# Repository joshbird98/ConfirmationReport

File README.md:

"# ConfirmationReport" 
Appendix A1 for confirmation report 
"Developments in Ion Beam Technology for Isotope Engineering at Ultra-Low Energy"
Contains hardware and software design files.

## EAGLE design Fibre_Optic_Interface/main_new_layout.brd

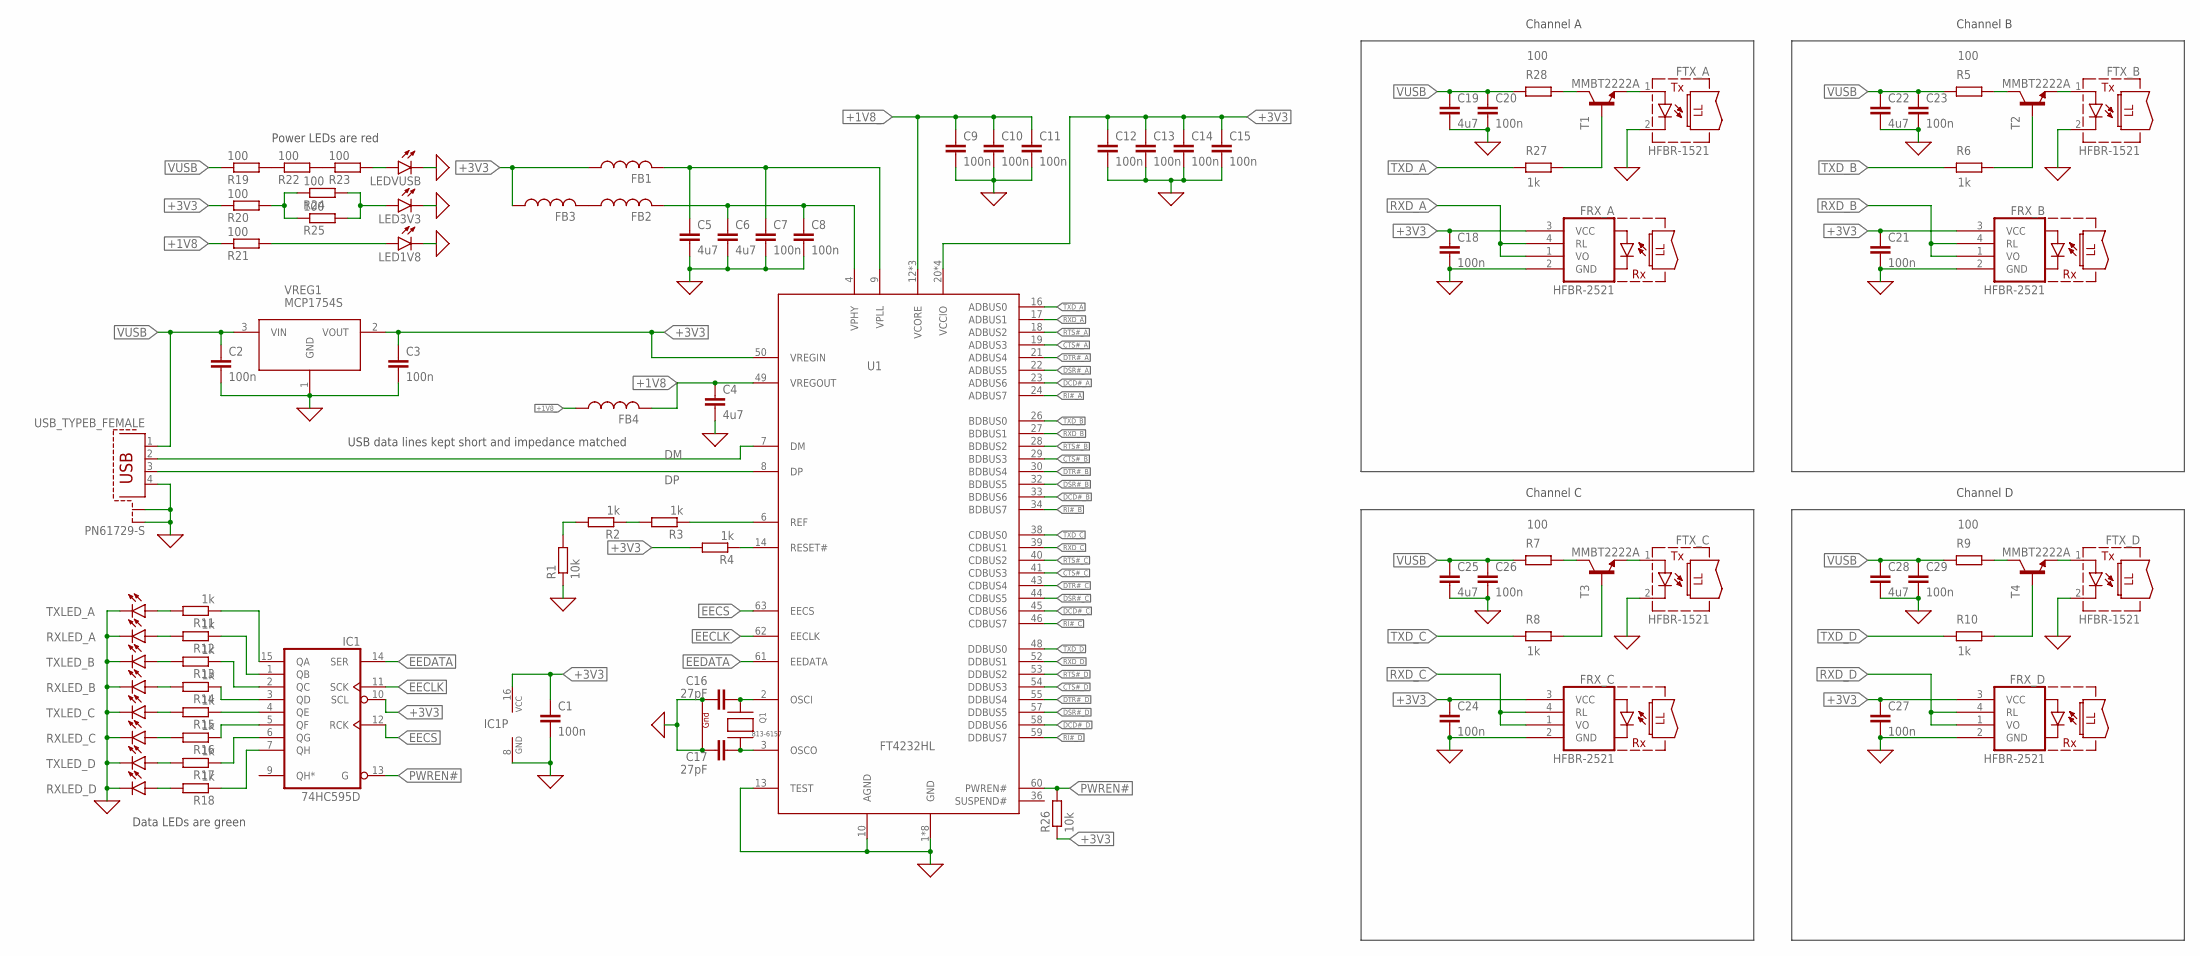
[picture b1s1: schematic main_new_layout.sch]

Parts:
C1, C2, C3, C7, C8, C9, C10, C11, C12, C13, C14, C15, C18, C20, C21, C23, C24, C26, C27, C29: 100n; C0805
C4, C5, C6, C19, C22, C25, C28: 4u7; C0805
C16, C17: 27pF; C0805
FB1, FB2, FB3, FB4: FERRITE; R0805
FRX_A: HFBR-2521; HFBR-15X3
FRX_B: HFBR-2521; HFBR-15X3
FRX_C: HFBR-2521; HFBR-15X3
FRX_D: HFBR-2521; HFBR-15X3
FTX_A: HFBR-1521; HFBR-15X3
FTX_B: HFBR-1521; HFBR-15X3
FTX_C: HFBR-1521; HFBR-15X3
FTX_D: HFBR-1521; HFBR-15X3
IC1: 74HC595D; SO16
LED1V8, LED3V3: LEDCHIP-LED0805; CHIP-LED0805
LEDVUSB: LEDCHIP-LED0805; CHIP-LED0805
Q1: XTAL-4-3225; NX3225
R1, R26: 10k; R0805
R2, R3, R4, R6, R8, R10, R11, R12, R13, R14, R15, R16, R17, R18, R27: 1k; R0805
R5, R7, R9, R19, R20, R21, R22, R23, R24, R25, R28: 100; R0805
RXLED_A: LEDCHIP-LED0805; CHIP-LED0805
RXLED_B: LEDCHIP-LED0805; CHIP-LED0805
RXLED_C: LEDCHIP-LED0805; CHIP-LED0805
RXLED_D: LEDCHIP-LED0805; CHIP-LED0805
T1, T2, T3, T4: MMBT2222A; SOT23-BEC
TXLED_A: LEDCHIP-LED0805; CHIP-LED0805
TXLED_B: LEDCHIP-LED0805; CHIP-LED0805
TXLED_C: LEDCHIP-LED0805; CHIP-LED0805
TXLED_D: LEDCHIP-LED0805; CHIP-LED0805
U1: FT4232HL; LQFP-ST-64-2
USB_TYPEB_FEMALE: PN61729-S
VREG1: MCP1754S; SOT23

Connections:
0: C1.2, C2.2, C3.2, C4.2, C5.2, C6.2, C7.2, C8.2, C9.2, C10.2, C11.2, C12.2, C13.2, C14.2, C15.2, C16.2, C17.2, C18.2, C19.2, C20.2, C21.2, C22.2, C23.2, C24.2, C25.2, C26.2, C27.2, C28.2, C29.2, FRX_A.2 (GND), FRX_B.2 (GND), FRX_C.2 (GND), FRX_D.2 (GND), FTX_A.2 (C), FTX_B.2 (C), FTX_C.2 (C), FTX_D.2 (C), IC1.8 (GND), LED1V8.C, LED3V3.C, LEDVUSB.C, Q1.2 (G2), Q1.4 (G1), R1.1, RXLED_A.C, RXLED_B.C, RXLED_C.C, RXLED_D.C, TXLED_A.C, TXLED_B.C, TXLED_C.C, TXLED_D.C, U1.1 (GND), U1.5 (GND), U1.10 (AGND), U1.11 (GND), U1.13 (TEST), U1.15 (GND), U1.25 (GND), U1.35 (GND), U1.47 (GND), U1.51 (GND), USB_TYPEB_FEMALE.4, USB_TYPEB_FEMALE.S1, USB_TYPEB_FEMALE.S2, VREG1.1 (GND)
+1V8: C4.1, FB4.2, R21.1, U1.49 (VREGOUT)
+1V8_: C9.1, C10.1, C11.1, FB4.1, U1.12 (VCORE), U1.37 (VCORE), U1.64 (VCORE)
+3V3: C1.1, C3.1, C12.1, C13.1, C14.1, C15.1, C18.1, C21.1, C24.1, C27.1, FB1.1, FB3.1, FRX_A.3 (VCC), FRX_B.3 (VCC), FRX_C.3 (VCC), FRX_D.3 (VCC), IC1.10 (SCL), IC1.16 (VCC), R4.2, R20.1, R26.1, U1.20 (VCCIO), U1.31 (VCCIO), U1.42 (VCCIO), U1.50 (VREGIN), U1.56 (VCCIO), VREG1.2 (VOUT)
CTS#_A: U1.19 (ADBUS3)
CTS#_B: U1.29 (BDBUS3)
CTS#_C: U1.41 (CDBUS3)
CTS#_D: U1.54 (DDBUS3)
DCD#_A: U1.23 (ADBUS6)
DCD#_B: U1.33 (BDBUS6)
DCD#_C: U1.45 (CDBUS6)
DCD#_D: U1.58 (DDBUS6)
DM: U1.7 (DM), USB_TYPEB_FEMALE.2
DP: U1.8 (DP), USB_TYPEB_FEMALE.3
DSR#_A: U1.22 (ADBUS5)
DSR#_B: U1.32 (BDBUS5)
DSR#_C: U1.44 (CDBUS5)
DSR#_D: U1.57 (DDBUS5)
DTR#_A: U1.21 (ADBUS4)
DTR#_B: U1.30 (BDBUS4)
DTR#_C: U1.43 (CDBUS4)
DTR#_D: U1.55 (DDBUS4)
EECLK: IC1.11 (SCK), U1.62 (EECLK)
EECS: IC1.12 (RCK), U1.63 (EECS)
EEDATA: IC1.14 (SER), U1.61 (EEDATA)
unnamed: LEDVUSB.A, R23.2
unnamed: LED3V3.A, R24.2, R25.2
unnamed: R27.2, T1.B
unnamed: C5.1, C7.1, FB1.2, U1.9 (VPLL)
unnamed: C6.1, C8.1, FB2.2, U1.4 (VPHY)
unnamed: R28.2, T1.C
unnamed: C17.1, Q1.3 (X2), U1.3 (OSCO)
unnamed: C16.1, Q1.1 (X1), U1.2 (OSCI)
unnamed: R3.1, U1.6 (REF)
unnamed: R4.1, U1.14 (RESET#)
unnamed: R2.1, R3.2
unnamed: R1.2, R2.2
unnamed: R6.2, T2.B
unnamed: R5.2, T2.C
unnamed: FTX_B.1 (A), T2.E
unnamed: FTX_A.1 (A), T1.E
unnamed: R8.2, T3.B
unnamed: R7.2, T3.C
unnamed: FTX_C.1 (A), T3.E
unnamed: R10.2, T4.B
unnamed: R9.2, T4.C
unnamed: FTX_D.1 (A), T4.E
unnamed: FB2.1, FB3.2
unnamed: IC1.15 (QA), R11.1
unnamed: IC1.1 (QB), R12.1
unnamed: IC1.2 (QC), R13.1
unnamed: LED1V8.A, R21.2
unnamed: IC1.3 (QD), R14.1
unnamed: IC1.4 (QE), R15.1
unnamed: IC1.5 (QF), R16.1
unnamed: IC1.6 (QG), R17.1
unnamed: IC1.7 (QH), R18.1
unnamed: R19.2, R22.1
unnamed: R11.2, TXLED_A.A
unnamed: R12.2, RXLED_A.A
unnamed: R13.2, TXLED_B.A
unnamed: R14.2, RXLED_B.A
unnamed: R15.2, TXLED_C.A
unnamed: R16.2, RXLED_C.A
unnamed: R17.2, TXLED_D.A
unnamed: R18.2, RXLED_D.A
unnamed: R22.2, R23.1
unnamed: R20.2, R24.1, R25.1
PWREN#: IC1.13 (G), R26.2, U1.60 (PWREN#)
RI#_A: U1.24 (ADBUS7)
RI#_B: U1.34 (BDBUS7)
RI#_C: U1.46 (CDBUS7)
RI#_D: U1.59 (DDBUS7)
RTS#_A: U1.18 (ADBUS2)
RTS#_B: U1.28 (BDBUS2)
RTS#_C: U1.40 (CDBUS2)
RTS#_D: U1.53 (DDBUS2)
RXD_A: FRX_A.1 (VO), FRX_A.4 (RL), U1.17 (ADBUS1)
RXD_B: FRX_B.1 (VO), FRX_B.4 (RL), U1.27 (BDBUS1)
RXD_C: FRX_C.1 (VO), FRX_C.4 (RL), U1.39 (CDBUS1)
RXD_D: FRX_D.1 (VO), FRX_D.4 (RL), U1.52 (DDBUS1)
TXD_A: R27.1, U1.16 (ADBUS0)
TXD_B: R6.1, U1.26 (BDBUS0)
TXD_C: R8.1, U1.38 (CDBUS0)
TXD_D: R10.1, U1.48 (DDBUS0)
VUSB: C2.1, C19.1, C20.1, C22.1, C23.1, C25.1, C26.1, C28.1, C29.1, R5.1, R7.1, R9.1, R19.1, R28.1, USB_TYPEB_FEMALE.1, VREG1.3 (VIN)

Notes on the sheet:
USB data lines kept short and impedance matched
Channel A
Channel B
Channel C
Channel D
Power LEDs are red
Data LEDs are green
813-6157

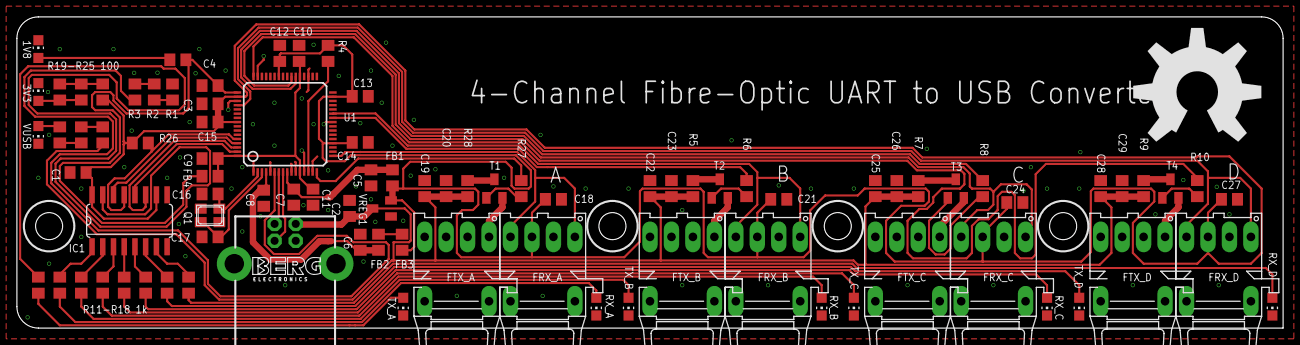
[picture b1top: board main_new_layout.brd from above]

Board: 2 copper layers, 149.9 x 36.8 mm, 89 parts (0 on the bottom side), 62 nets.

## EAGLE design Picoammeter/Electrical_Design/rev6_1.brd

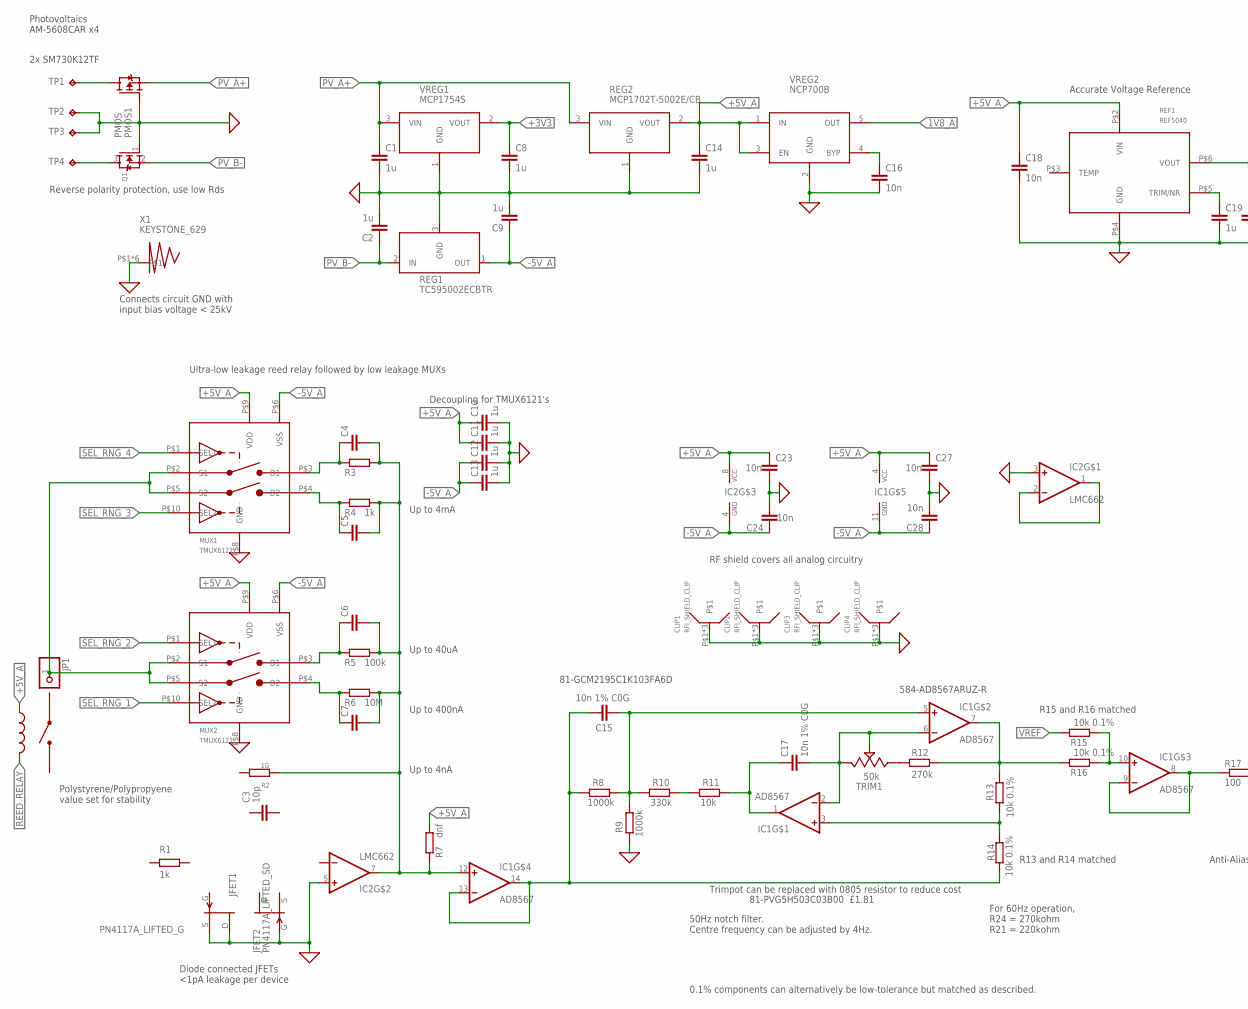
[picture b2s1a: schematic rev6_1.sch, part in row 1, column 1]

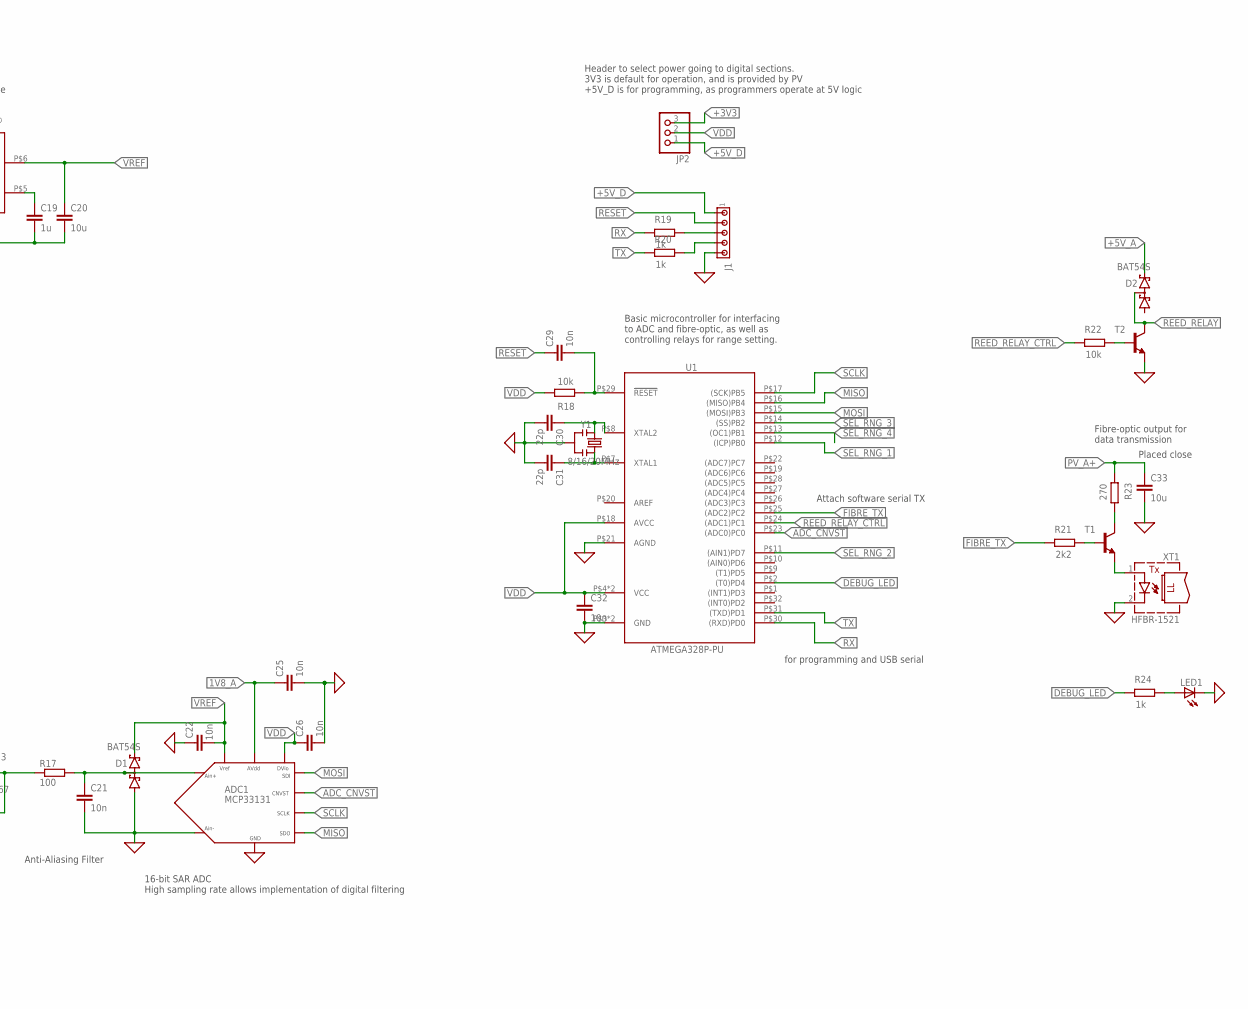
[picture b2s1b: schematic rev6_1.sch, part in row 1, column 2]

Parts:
ADC1: MCP33131; MSOP10
C1, C2, C8, C9, C10, C11, C12, C13, C14, C19: 1u; C0805
C4, C5, C6, C7: C-EUC0805; C0805
C15, C17: 10n 1% C0G; C1206
C16, C18, C21, C22, C23, C24, C25, C26, C27, C28, C29, C32: 10n; C0805
C20, C33: 10u; C0805
C30, C31: 22p; C0805
CLIP1, CLIP2, CLIP3, CLIP4: RFI_SHIELD_CLIP
D1, D2: BAT54S; SOT23
IC1: AD8567; TSSOP14
IC2: LMC662; DIL8_LIFTED
J1: MTA05-100; 10X05MTA
JFET1: PN4117A_LIFTED_G; TO-92_LIFTED_GATE
JFET2: PN4117A_LIFTED_SD; TO92_LIFTED_SOURCE_DRAIN
JP1: PINHD-1X1; 1X01
JP2: PINHD-1X3; 1X03
LED1: LEDCHIPLED_0805; CHIPLED_0805
MUX1, MUX2: TMUX6121; VSSOP-10
PMOS1: PMOS; SOT23
Q1: MOSFET-NREFLOW; SOT23
R2: 1G; 1GOHM_HALF_LIFTED
R3: R-EU_R0805; R0805
R4, R19, R20, R24: 1k; R0805
R5: 100k; R0805
R6: 10M; R0805
R7: dnf; R0805
R8, R9: 1000k; R0805
R10: 330k; R0805
R11, R18, R22: 10k; R0805
R12: 270k; R0805
R13, R14, R15, R16: 10k 0.1%; R0805
R17: 100; R0805
R21: 2k2; R0805
R23: 270; R0805
REF1: REF5040; VSSOP-8_
REG1: TC595002ECBTR; SOT23
REG2: MCP1702T-5002E/CB; SOT23
RLY1: HI05-1A66_REED_RELAY; HI05-1A66
T1, T2: BC847A-NPN-SOT23-BEC; SOT23-BEC
TP1, TP2, TP3, TP4: TPPAD1-13; P1-13
TRIM1: 50k; PVG5H
U1: ATMEGA328P-PU; TQFP-32
VREG1: MCP1754S; SOT23
VREG2: NCP700B; TSOP-5
X1: KEYSTONE_629; SPRING_CONTACT
XT1: HFBR-1521; HFBR-15X3
Y1: 8/16/20MHz; RESONATOR-SMD-1:1

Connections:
0: ADC1.4 (AIN-), ADC1.5 (GND), C1.2, C2.2, C8.2, C9.2, C10.2, C11.2, C12.2, C13.2, C14.2, C16.2, C18.2, C19.2, C20.2, C21.2, C22.1, C23.2, C24.2, C25.2, C26.2, C27.2, C28.2, C30.2, C31.2, C32.2, C33.2, CLIP1.P$1, CLIP1.P$2, CLIP1.P$3, CLIP2.P$1, CLIP2.P$2, CLIP2.P$3, CLIP3.P$1, CLIP3.P$2, CLIP3.P$3, CLIP4.P$1, CLIP4.P$2, CLIP4.P$3, D1.1 (A1), IC2.3 (+IN), IC2.5 (+IN), J1.5, JFET1.P$2 (D), JFET1.P$3 (S), JFET2.P$1, LED1.C, MUX1.P$8 (GND), MUX2.P$8 (GND), PMOS1.1 (G), Q1.1 (G), R9.1, REF1.P$4 (GND), REG1.3 (GND), REG2.1 (GND), T2.E, TP2.TP, TP3.TP, U1.P$3 (GND), U1.P$5 (GND), U1.P$21 (AGND), VREG1.1 (GND), VREG2.2 (GND), X1.P$1, X1.P$2, X1.P$3, X1.P$4, X1.P$5, X1.P$6, XT1.2 (C), Y1.2
1V8_A: ADC1.2 (AVDD), C25.1, VREG2.5 (OUT)
+3V3: C8.1, JP2.3, VREG1.2 (VOUT)
+5V_A: C10.1, C11.1, C14.1, C18.1, C23.1, C27.1, D2.2 (C2), IC1.4 (VCC), IC2.8 (VCC), MUX1.P$9 (VDD), MUX2.P$9 (VDD), R7.2, REF1.P$2 (VIN), REG2.2 (VOUT), RLY1.P$5, VREG2.1 (IN), VREG2.3 (EN)
+5V_D: J1.1, JP2.1
-5V_A: C9.1, C12.1, C13.1, C24.1, C28.1, IC1.11 (GND), IC2.4 (GND), MUX1.P$6 (VSS), MUX2.P$6 (VSS), REG1.1 (OUT)
ADC_CNVST: ADC1.6 (CNVST), U1.P$23 ((ADC0)PC0)
DEBUG_LED: R24.1, U1.P$2 ((T0)PD4)
FIBRE_TX: R21.1, U1.P$25 ((ADC2)PC2)
MISO: ADC1.7 (SDO), U1.P$16 ((MISO)PB4)
MOSI: ADC1.9 (SDI), U1.P$15 ((MOSI)PB3)
unnamed: IC2.1 (OUT), IC2.2 (-IN)
unnamed: IC1.8 (OUT), IC1.9 (-IN), R17.1
unnamed: R21.2, T1.B
unnamed: IC1.10 (+IN), R15.2, R16.2
unnamed: ADC1.3 (AIN+), C21.1, D1.3 (C1A2), R17.2
unnamed: R23.2, T1.C
unnamed: C30.1, U1.P$8 (XTAL2), Y1.1
unnamed: C19.1, REF1.P$5 (TRIM/NR)
unnamed: C31.1, U1.P$7 (XTAL1), Y1.3
unnamed: JP1.1, MUX1.P$2 (S1), MUX1.P$5 (S2), MUX2.P$2 (S1), MUX2.P$5 (S2)
unnamed: C4.1, MUX1.P$3 (D1), R3.1
unnamed: R22.2, T2.B
unnamed: C17.2, IC1.2 (-IN), IC1.6 (-IN), TRIM1.B (E), TRIM1.W (S)
unnamed: T1.E, XT1.1 (A)
unnamed: IC1.7 (OUT), R12.2, R13.1, R16.1
unnamed: R10.2, R11.1
unnamed: IC1.3 (+IN), R13.2, R14.1
unnamed: C4.2, C5.2, C6.2, C7.2, IC1.12 (+IN), IC2.7 (OUT), R2.2, R3.2, R4.2, R5.2, R6.2, R7.1
unnamed: C15.1, IC1.13 (-IN), IC1.14 (OUT), R8.1, R14.2
unnamed: C29.2, R18.1, U1.P$29 (!RESET)
unnamed: C15.2, IC1.5 (+IN), R8.2, R9.2, R10.1
unnamed: LED1.A, R24.2
unnamed: C16.1, VREG2.4 (BYP)
unnamed: C7.1, MUX2.P$4 (D2), R6.1
unnamed: J1.3, R19.2
unnamed: J1.4, R20.2
unnamed: C6.1, MUX2.P$3 (D1), R5.1
unnamed: C5.1, MUX1.P$4 (D2), R4.1
unnamed: R12.1, TRIM1.A
unnamed: Q1.3 (D), TP4.TP
unnamed: C17.1, IC1.1 (OUT), R11.2
unnamed: PMOS1.3 (D), TP1.TP
PV_A+: C1.1, C33.1, PMOS1.2 (S), R23.1, REG2.3 (VIN), VREG1.3 (VIN)
PV_B-: C2.1, Q1.2 (S), REG1.2 (IN)
REED_RELAY: D2.3 (C1A2), RLY1.P$3, T2.C
REED_RELAY_CTRL: R22.1, U1.P$24 ((ADC1)PC1)
RESET: C29.1, J1.2
RX: R19.1, U1.P$30 ((RXD)PD0)
SCLK: ADC1.8 (SCLK), U1.P$17 ((SCK)PB5)
SEL_RNG_1: MUX2.P$10 (SEL2), U1.P$12 ((ICP)PB0)
SEL_RNG_2: MUX2.P$1 (SEL1), U1.P$11 ((AIN1)PD7)
SEL_RNG_3: MUX1.P$10 (SEL2), U1.P$14 ((SS)PB2)
SEL_RNG_4: MUX1.P$1 (SEL1), U1.P$13 ((OC1)PB1)
TX: R20.1, U1.P$31 ((TXD)PD1)
VDD: ADC1.10 (DVIO), C26.1, C32.1, JP2.2, R18.2, U1.P$4 (VCC), U1.P$6 (VCC), U1.P$18 (AVCC)
VREF: ADC1.1 (VREF), C20.1, C22.2, D1.2 (C2), R15.1, REF1.P$6 (VOUT)

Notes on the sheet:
Diode connected JFETs <1pA leakage per device
Ultra-low leakage reed relay followed by low leakage MUXs
RF shield covers all analog circuitry
Photovoltaics AM-5608CAR x4
Header to select power going to digital sections. 3V3 is default for operation, and is provided by PV +5V_D is for programming, as programmers operate at 5V logic
Placed close
for programming and USB serial
Polystyrene/Polypropyene value set for stability
Anti-Aliasing Filter
Connects circuit GND with input bias voltage < 25kV
Accurate Voltage Reference
16-bit SAR ADC High sampling rate allows implementation of digital filtering
Basic microcontroller for interfacing to ADC and fibre-optic, as well as controlling relays for range setting.
Up to 4mA
Up to 40uA
Up to 400nA
Up to 4nA
Fibre-optic output for data transmission
Attach software serial TX
Trimpot can be replaced with 0805 resistor to reduce cost
81-PVG5H503C03B00 £1.81
81-GCM2195C1K103FA6D
50Hz notch filter. Centre frequency can be adjusted by 4Hz.
584-AD8567ARUZ-R
2x SM730K12TF
Reverse polarity protection, use low Rds
For 60Hz operation, R24 = 270kohm R21 = 220kohm
R13 and R14 matched
R15 and R16 matched
0.1% components can alternatively be low-tolerance but matched as described.
Decoupling for TMUX6121's

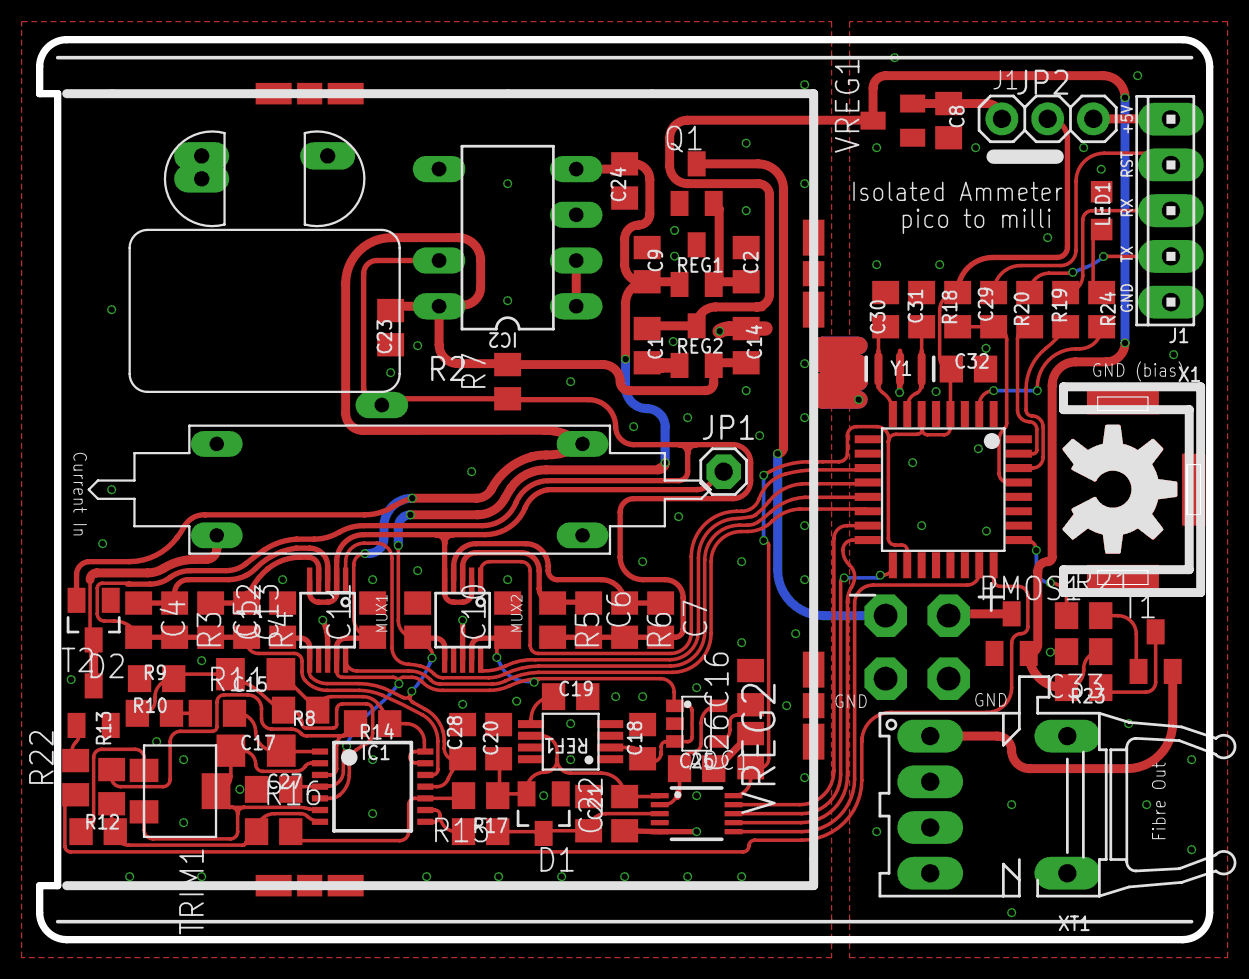
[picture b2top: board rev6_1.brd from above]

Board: 2 copper layers, 65.0 x 50.0 mm, 91 parts (0 on the bottom side), 57 nets.

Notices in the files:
parts and their libraries:
SparkFun-Clocks: Licensing: Creative Commons ShareAlike 4.0 International - https://creativecommons.org/licenses/by-sa/4.0
